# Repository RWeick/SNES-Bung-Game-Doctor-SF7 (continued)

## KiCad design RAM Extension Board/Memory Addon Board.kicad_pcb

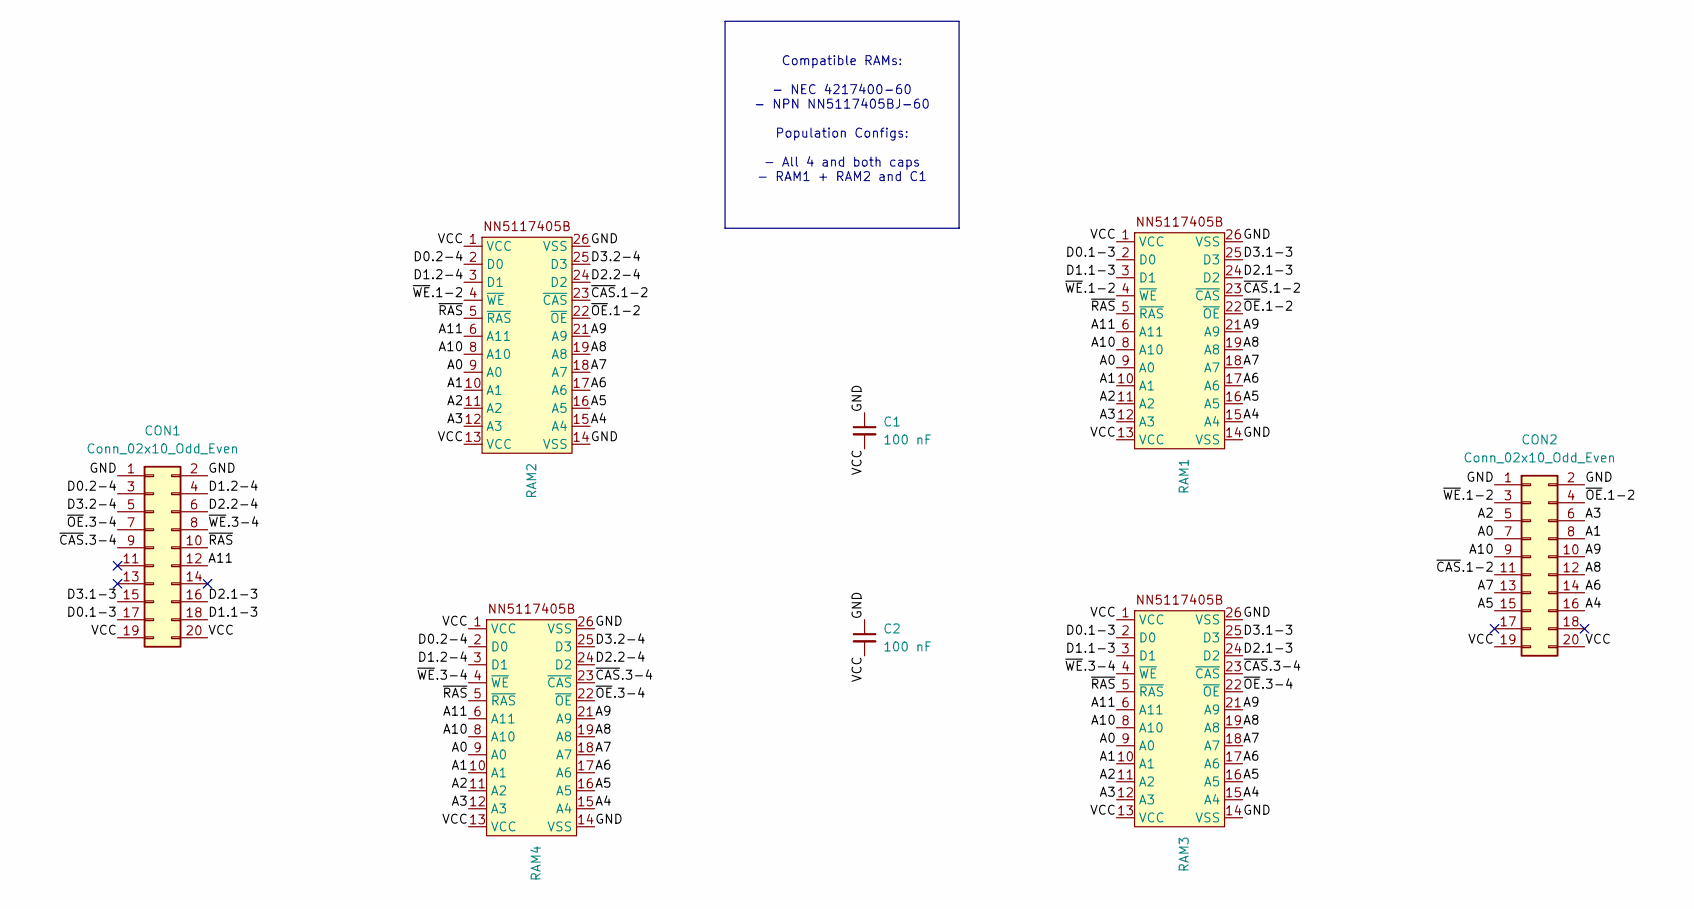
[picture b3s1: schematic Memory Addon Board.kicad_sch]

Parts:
C1, C2: 100 nF; SMD Passive
CON1, CON2: Conn_02x10_Odd_Even; PinHeader_2x10_P2.54mm_Vertical
RAM1, RAM2, RAM3, RAM4: RAM

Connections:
/A0: CON2.7, RAM1.9 (A0), RAM2.9 (A0), RAM3.9 (A0), RAM4.9 (A0)
/A1: CON2.8, RAM1.10 (A1), RAM2.10 (A1), RAM3.10 (A1), RAM4.10 (A1)
/A2: CON2.5, RAM1.11 (A2), RAM2.11 (A2), RAM3.11 (A2), RAM4.11 (A2)
/A3: CON2.6, RAM1.12 (A3), RAM2.12 (A3), RAM3.12 (A3), RAM4.12 (A3)
/A4: CON2.16, RAM1.15 (A4), RAM2.15 (A4), RAM3.15 (A4), RAM4.15 (A4)
/A5: CON2.15, RAM1.16 (A5), RAM2.16 (A5), RAM3.16 (A5), RAM4.16 (A5)
/A6: CON2.14, RAM1.17 (A6), RAM2.17 (A6), RAM3.17 (A6), RAM4.17 (A6)
/A7: CON2.13, RAM1.18 (A7), RAM2.18 (A7), RAM3.18 (A7), RAM4.18 (A7)
/A8: CON2.12, RAM1.19 (A8), RAM2.19 (A8), RAM3.19 (A8), RAM4.19 (A8)
/A9: CON2.10, RAM1.21 (A9), RAM2.21 (A9), RAM3.21 (A9), RAM4.21 (A9)
/A10: CON2.9, RAM1.8 (A10), RAM2.8 (A10), RAM3.8 (A10), RAM4.8 (A10)
/A11: CON1.12, RAM1.6 (A11), RAM2.6 (A11), RAM3.6 (A11), RAM4.6 (A11)
/D0.1-3: CON1.17, RAM1.2 (D0), RAM3.2 (D0)
/D0.2-4: CON1.3, RAM2.2 (D0), RAM4.2 (D0)
/D1.1-3: CON1.18, RAM1.3 (D1), RAM3.3 (D1)
/D1.2-4: CON1.4, RAM2.3 (D1), RAM4.3 (D1)
/D2.1-3: CON1.16, RAM1.24 (D2), RAM3.24 (D2)
/D2.2-4: CON1.6, RAM2.24 (D2), RAM4.24 (D2)
/D3.1-3: CON1.15, RAM1.25 (D3), RAM3.25 (D3)
/D3.2-4: CON1.5, RAM2.25 (D3), RAM4.25 (D3)
/GND: C1.1, C2.1, CON1.1, CON1.2, CON2.1, CON2.2, RAM1.14 (VSS), RAM1.26 (VSS), RAM2.14 (VSS), RAM2.26 (VSS), RAM3.14 (VSS), RAM3.26 (VSS), RAM4.14 (VSS), RAM4.26 (VSS)
/VCC: C1.2, C2.2, CON1.19, CON1.20, CON2.19, CON2.20, RAM1.1 (VCC), RAM1.13 (VCC), RAM2.1 (VCC), RAM2.13 (VCC), RAM3.1 (VCC), RAM3.13 (VCC), RAM4.1 (VCC), RAM4.13 (VCC)
/~CAS.1-2: CON2.11, RAM1.23 (~CAS), RAM2.23 (~CAS)
/~CAS.3-4: CON1.9, RAM3.23 (~CAS), RAM4.23 (~CAS)
/~OE.1-2: CON2.4, RAM1.22 (~OE), RAM2.22 (~OE)
/~OE.3-4: CON1.7, RAM3.22 (~OE), RAM4.22 (~OE)
/~RAS: CON1.10, RAM1.5 (~RAS), RAM2.5 (~RAS), RAM3.5 (~RAS), RAM4.5 (~RAS)
/~WE.1-2: CON2.3, RAM1.4 (~WE), RAM2.4 (~WE)
/~WE.3-4: CON1.8, RAM3.4 (~WE), RAM4.4 (~WE)

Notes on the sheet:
Compatible RAMs: - NEC 4217400-60 - NPN NN5117405BJ-60 Population Configs: - All 4 and both caps - RAM1 + RAM2 and C1

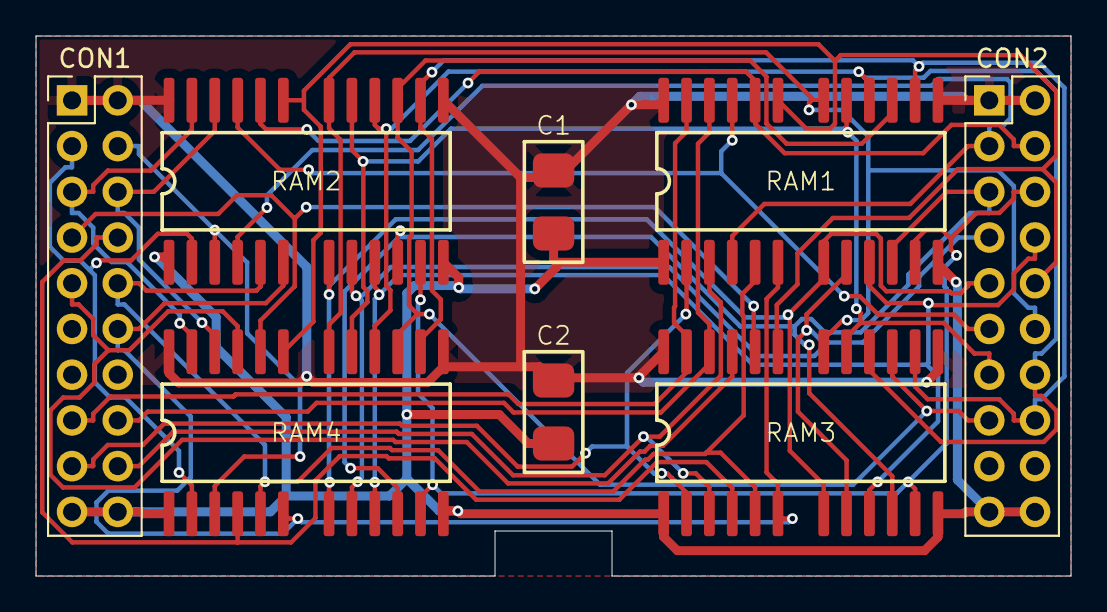
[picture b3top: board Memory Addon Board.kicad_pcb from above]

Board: 2 copper layers, 57.5 x 30.0 mm, 8 parts (0 on the bottom side), 29 nets.

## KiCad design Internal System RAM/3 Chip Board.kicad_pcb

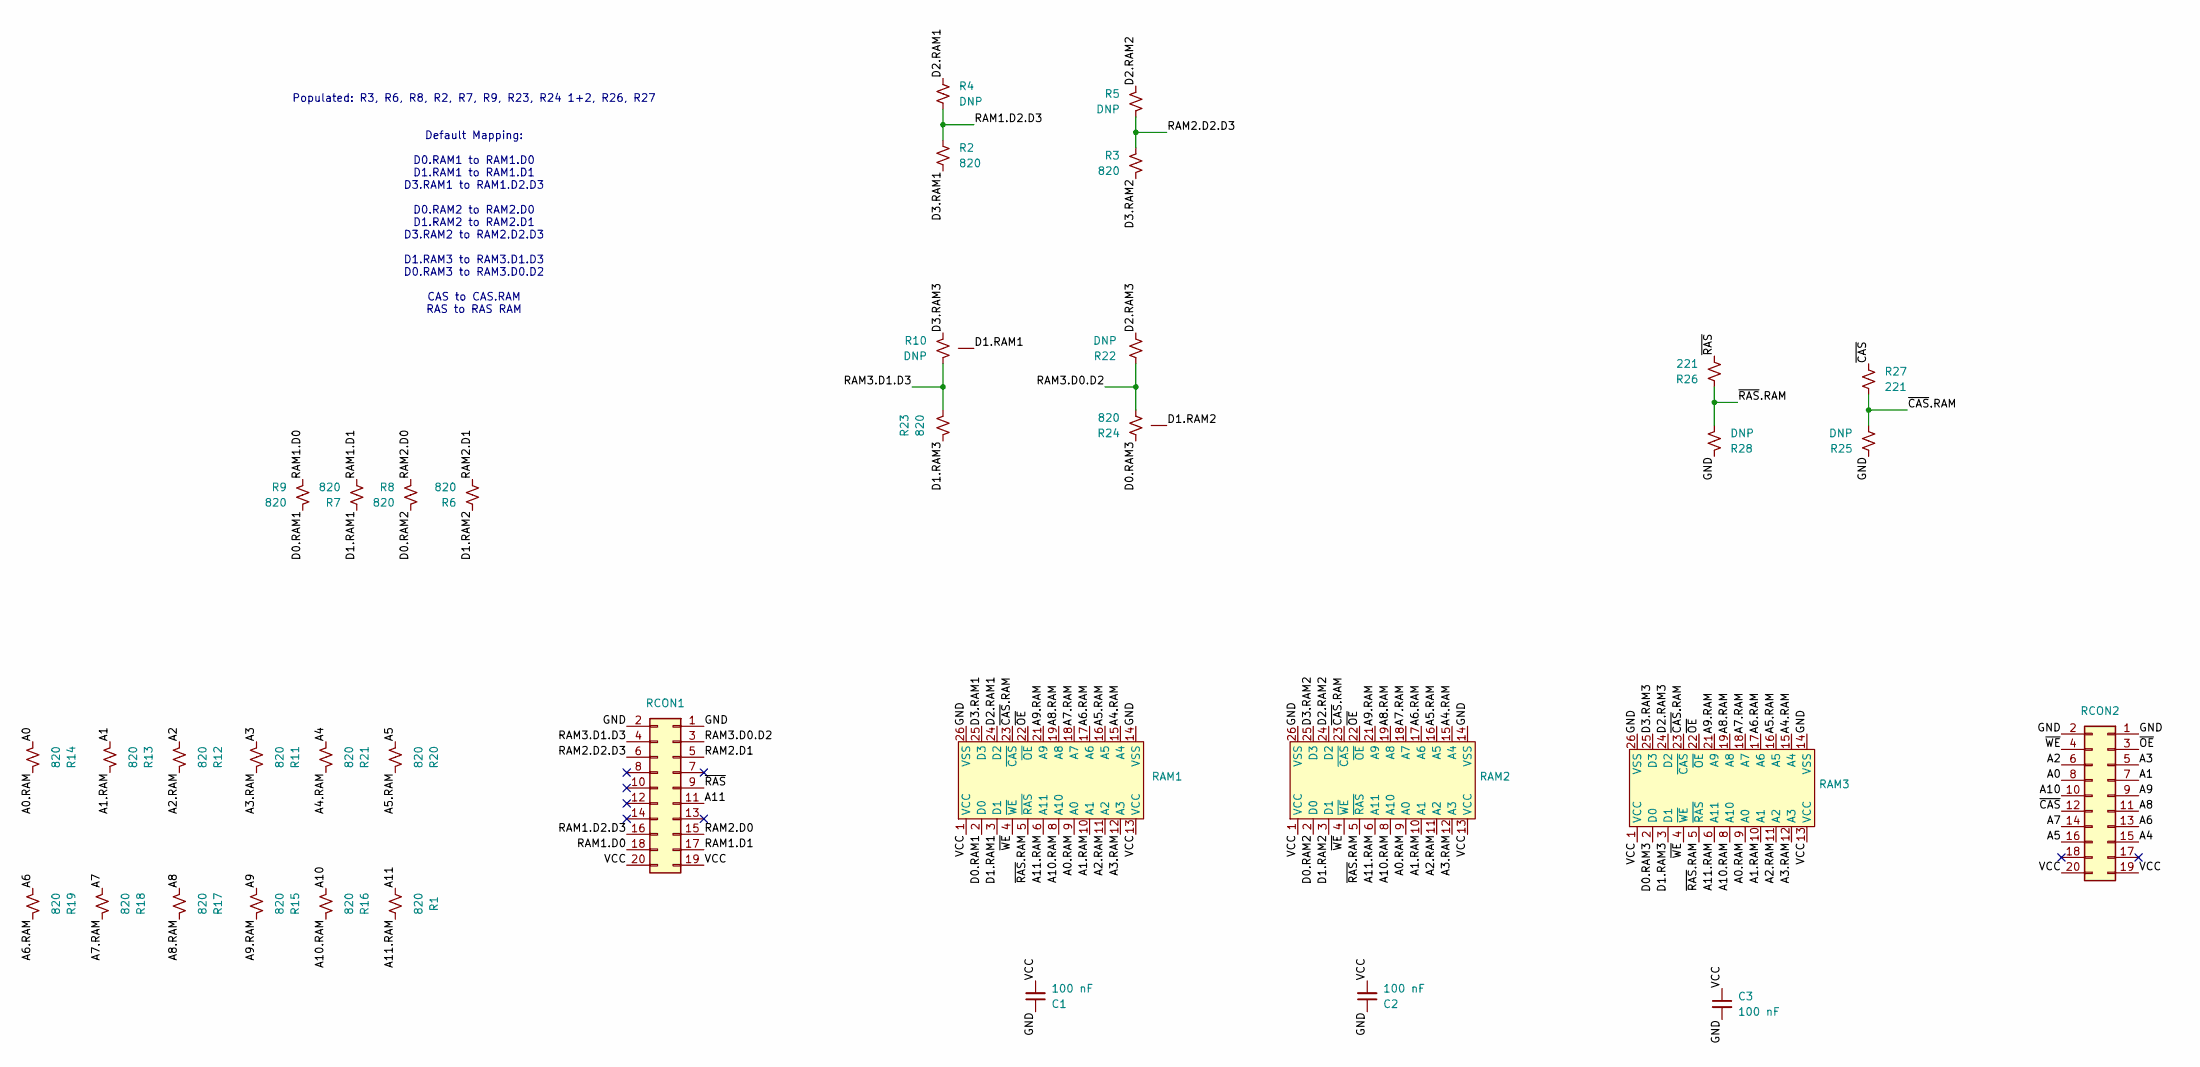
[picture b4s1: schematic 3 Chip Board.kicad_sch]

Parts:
C1, C2, C3: 100 nF; SMD C
R1, R2, R3, R6, R7, R8, R9, R11, R12, R13, R14, R15, R16, R17, R18, R19, R20, R21, R23: 820; SMD R
R4, R5, R22, R25, R28: DNP; SMD R
R10: DNP; SMD R3
R24: 820; SMD R3
R26, R27: 221; SMD R
RAM1, RAM2, RAM3: RAM
RCON1, RCON2: Conn_02x10_Odd_Even; PinSocket_2x10_P2.54mm_Vertical

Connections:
/A0: R14.2, RCON2.8
/A0.RAM: R14.1, RAM1.9 (A0), RAM2.9 (A0), RAM3.9 (A0)
/A1: R13.2, RCON2.7
/A1.RAM: R13.1, RAM1.10 (A1), RAM2.10 (A1), RAM3.10 (A1)
/A2: R12.2, RCON2.6
/A2.RAM: R12.1, RAM1.11 (A2), RAM2.11 (A2), RAM3.11 (A2)
/A3: R11.2, RCON2.5
/A3.RAM: R11.1, RAM1.12 (A3), RAM2.12 (A3), RAM3.12 (A3)
/A4: R21.2, RCON2.15
/A4.RAM: R21.1, RAM1.15 (A4), RAM2.15 (A4), RAM3.15 (A4)
/A5: R20.2, RCON2.16
/A5.RAM: R20.1, RAM1.16 (A5), RAM2.16 (A5), RAM3.16 (A5)
/A6: R19.2, RCON2.13
/A6.RAM: R19.1, RAM1.17 (A6), RAM2.17 (A6), RAM3.17 (A6)
/A7: R18.2, RCON2.14
/A7.RAM: R18.1, RAM1.18 (A7), RAM2.18 (A7), RAM3.18 (A7)
/A8: R17.2, RCON2.11
/A8.RAM: R17.1, RAM1.19 (A8), RAM2.19 (A8), RAM3.19 (A8)
/A9: R15.2, RCON2.9
/A9.RAM: R15.1, RAM1.21 (A9), RAM2.21 (A9), RAM3.21 (A9)
/A10: R16.2, RCON2.10
/A10.RAM: R16.1, RAM1.8 (A10), RAM2.8 (A10), RAM3.8 (A10)
/A11: R1.1, RCON1.11
/A11.RAM: R1.2, RAM1.6 (A11), RAM2.6 (A11), RAM3.6 (A11)
/D0.RAM1: R9.2, RAM1.2 (D0)
/D0.RAM2: R8.2, RAM2.2 (D0)
/D0.RAM3: R24.1, RAM3.2 (D0)
/D1.RAM1: R7.1, R10.3 (Pad_3), RAM1.3 (D1)
/D1.RAM2: R6.1, R24.3 (Pad_3), RAM2.3 (D1)
/D1.RAM3: R23.2, RAM3.3 (D1)
/D2.RAM1: R4.2, RAM1.24 (D2)
/D2.RAM2: R5.2, RAM2.24 (D2)
/D2.RAM3: R22.1, RAM3.24 (D2)
/D3.RAM1: R2.2, RAM1.25 (D3)
/D3.RAM2: R3.2, RAM2.25 (D3)
/D3.RAM3: R10.1, RAM3.25 (D3)
/GND: C1.1, C2.1, C3.2, R25.2, R28.2, RAM1.14 (VSS), RAM1.26 (VSS), RAM2.14 (VSS), RAM2.26 (VSS), RAM3.14 (VSS), RAM3.26 (VSS), RCON1.1, RCON1.2, RCON2.1, RCON2.2
/RAM1.D0: R9.1, RCON1.18
/RAM1.D1: R7.2, RCON1.17
/RAM1.D2.D3: R2.1, R4.1, RCON1.16
/RAM2.D0: R8.1, RCON1.15
/RAM2.D1: R6.2, RCON1.5
/RAM2.D2.D3: R3.1, R5.1, RCON1.6
/RAM3.D0.D2: R22.2, R24.2, RCON1.3
/RAM3.D1.D3: R10.2, R23.1, RCON1.4
/VCC: C1.2, C2.2, C3.1, RAM1.1 (VCC), RAM1.13 (VCC), RAM2.1 (VCC), RAM2.13 (VCC), RAM3.1 (VCC), RAM3.13 (VCC), RCON1.19, RCON1.20, RCON2.19, RCON2.20
/~CAS: R27.1, RCON2.12
/~CAS.RAM: R25.1, R27.2, RAM1.23 (~CAS), RAM2.23 (~CAS), RAM3.23 (~CAS)
/~OE: RAM1.22 (~OE), RAM2.22 (~OE), RAM3.22 (~OE), RCON2.3
/~RAS: R26.2, RCON1.9
/~RAS.RAM: R26.1, R28.1, RAM1.5 (~RAS), RAM2.5 (~RAS), RAM3.5 (~RAS)
/~WE: RAM1.4 (~WE), RAM2.4 (~WE), RAM3.4 (~WE), RCON2.4

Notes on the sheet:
Populated: R3, R6, R8, R2, R7, R9, R23, R24 1+2, R26, R27 Default Mapping: D0.RAM1 to RAM1.D0 D1.RAM1 to RAM1.D1 D3.RAM1 to RAM1.D2.D3 D0.RAM2 to RAM2.D0 D1.RAM2 to RAM2.D1 D3.RAM2 to RAM2.D2.D3 D1.RAM3 to RAM3.D1.D3 D0.RAM3 to RAM3.D0.D2 CAS to CAS.RAM RAS to RAS RAM

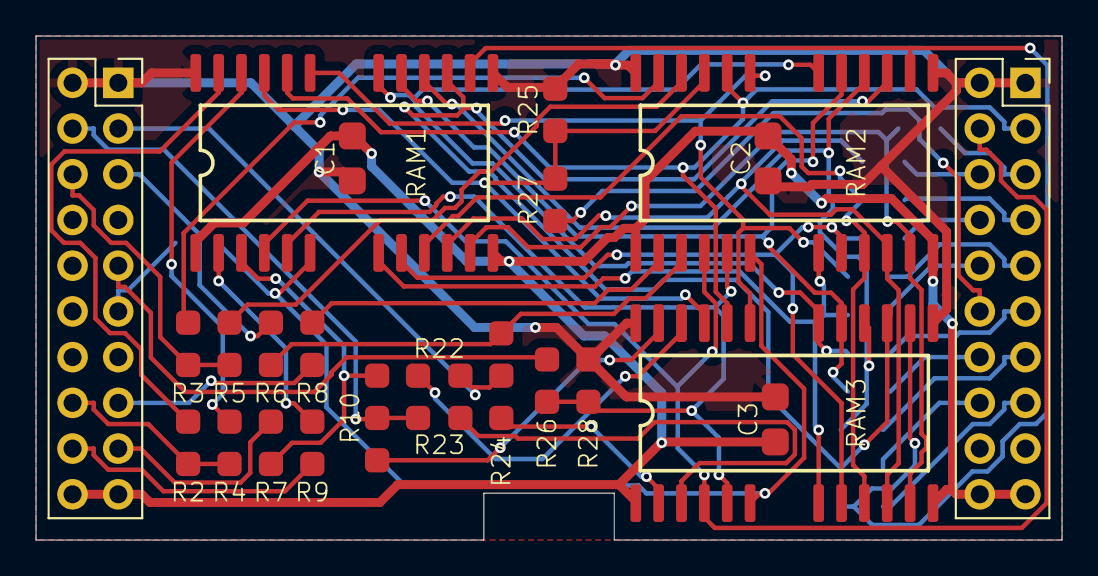
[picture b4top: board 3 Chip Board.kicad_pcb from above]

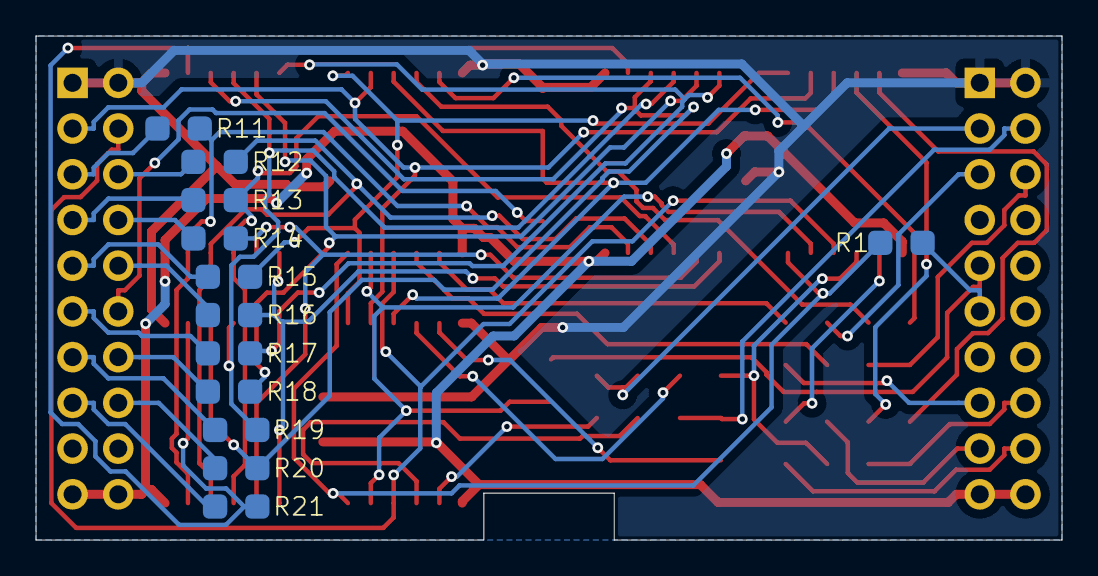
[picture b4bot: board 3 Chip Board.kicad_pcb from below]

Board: 2 copper layers, 57.0 x 28.0 mm, 36 parts (12 on the bottom side), 52 nets.
